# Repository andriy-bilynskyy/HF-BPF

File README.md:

# Short wave BPF

This is HW design of passive shortwave BPF 1.8MHz - 30MHz.

The schematic is based on 1.8MHz 7-th order elliptic HPF and 30MHz 7-th order elliptic LPF.

Input output filter resistance is 50 Ohms.

Loses in band-pass are less than -6.8dB. Loses at 60MHz and more are more than -80 dB. The same situation for frequencies lower than  1MHz - -80dB.

The design is created to use together with SDR receivers due to problematic reception of shot-wave bands in city conditions. This situation is mainly caused by huge noise from different switch power converters/inverters at low frequencies and FM radios at high frequencies.

## Folder structure

- **HF-BPF.asc** - LTspice simulation.  https://www.analog.com/en/design-center/design-tools-and-calculators/ltspice-simulator.html

- **HF-BPF.pro** - KiCad project. https://kicad.org/

- **HF-BPF.sch** - KiCad schematic.

- **HF-BPF.kicad_pcb** - KiCad PCB.

- **HF-BPF.net** - KiCad net-list file.

- **Manufacture** - Gerber files for PCB manufacturing. PCB manufacture https://www.elecrow.com/pcb-manufacturing.html

# Amplitude-frequency characteristic

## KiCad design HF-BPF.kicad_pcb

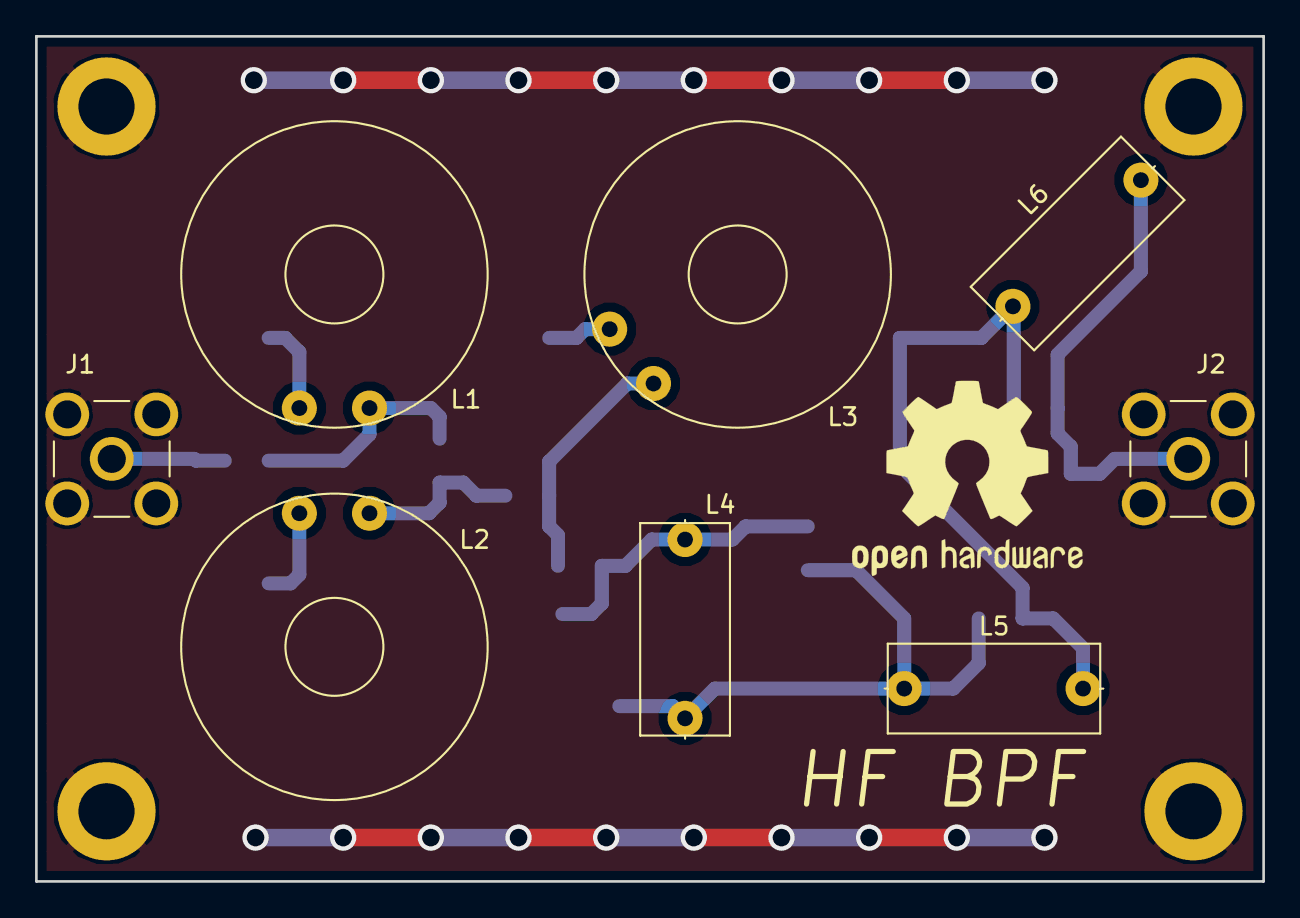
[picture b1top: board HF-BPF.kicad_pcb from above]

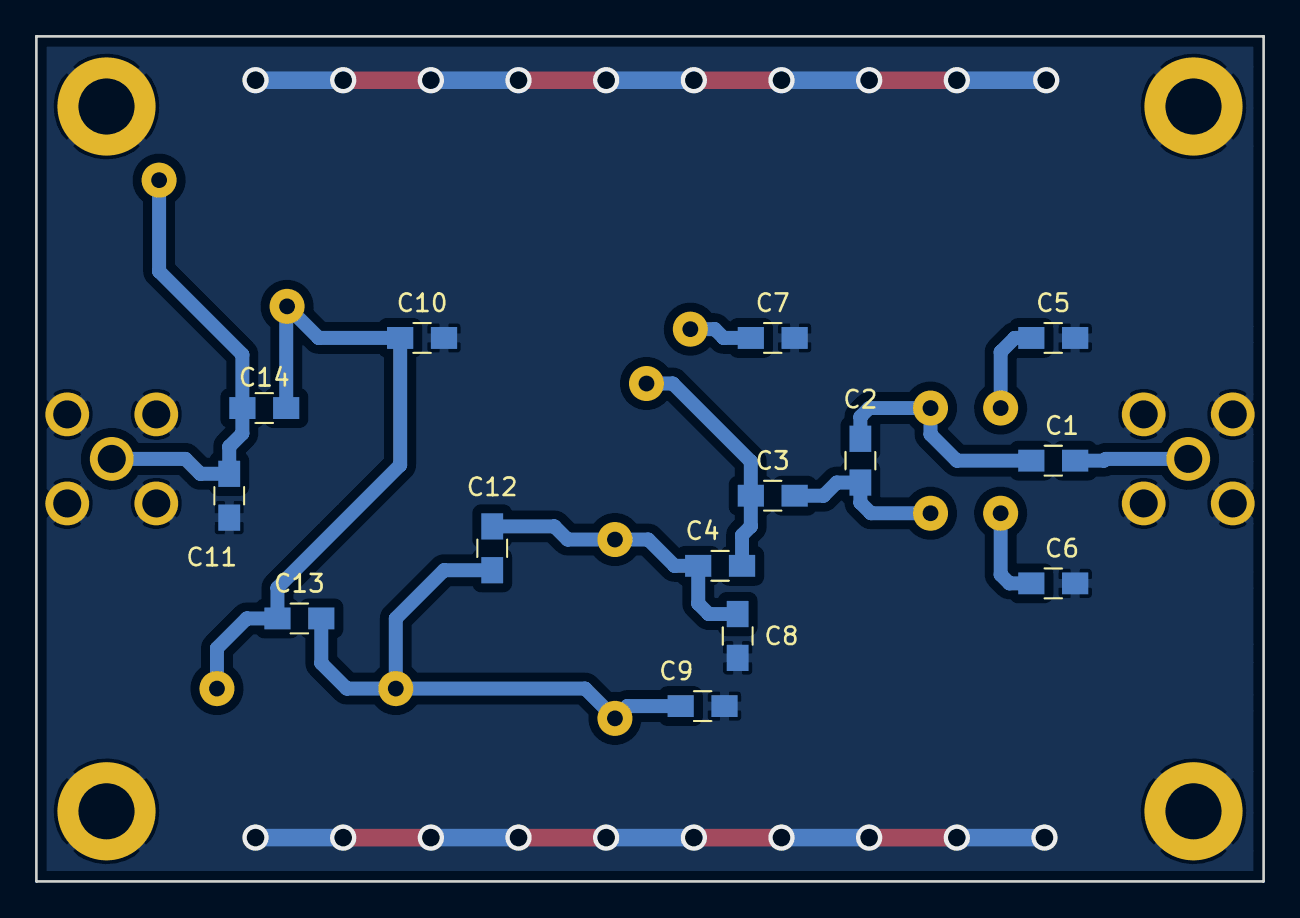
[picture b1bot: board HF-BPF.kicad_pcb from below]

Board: 2 copper layers, 70.0 x 48.2 mm, 22 parts (14 on the bottom side), 12 nets.

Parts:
C1, C4: 2.2nF; C_0805_HandSoldering
C2, C3: 1.5nF; C_0805_HandSoldering
C5: 33nF; C_0805_HandSoldering
C6, C7: 10nF; C_0805_HandSoldering
C8: 82pF; C_0805_HandSoldering
C9: 180pF; C_0805_HandSoldering
C10: 150pF; C_0805_HandSoldering
C11: 68pF; C_0805_HandSoldering
C12: 4.7pF; C_0805_HandSoldering
C13: 22pF; C_0805_HandSoldering
C14: 15pF; C_0805_HandSoldering
J1, J2: SMA-15; SMA_THT_Jack_Straight
L1: 3.2uH; L_Toroid_Horizontal_D17.3mm_P15.24mm_Bourns_2000
L2: 2.5uH; L_Toroid_Horizontal_D17.3mm_P15.24mm_Bourns_2000
L3: 3.6uH; L_Toroid_Horizontal_D17.3mm_P15.24mm_Bourns_2000
L4: 370nH; L_Axial_L12.0mm_D5.0mm_P15.24mm_Horizontal_Fastron_MISC
L5: 380nH; L_Axial_L12.0mm_D5.0mm_P15.24mm_Horizontal_Fastron_MISC
L6: 360nH; L_Axial_L12.0mm_D5.0mm_P15.24mm_Horizontal_Fastron_MISC

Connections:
GND: C5.1, C6.1, C7.1, C8.1, C9.1, C10.1, C11.1, J1.2, J2.2
unnamed: C1.1, C2.2, L1.1
unnamed: C1.2, J1.1
unnamed: C2.1, C3.2, L2.1
unnamed: C3.1, C4.2, L3.1
unnamed: C5.2, L1.2
unnamed: C6.2, L2.2
unnamed: C7.2, L3.2
unnamed: C10.2, C13.1, C14.2, L5.2, L6.1
unnamed: C11.2, C14.1, J2.1, L6.2
unnamed: C9.2, C12.1, C13.2, L4.2, L5.1
unnamed: C4.1, C8.2, C12.2, L4.1

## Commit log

2020-02-11 Initial commit.
    Calculations based on:
    https://vpayaem.ru/information6_2.html
2020-02-11 Add gitingore for generated files.
2020-02-12 Add inductors data.
    Calculations based on:
    https://coil32.net/
2020-02-12 Add PCB artwork.
2020-02-13 Add manufacture files.
2020-02-13 Add License and readme.
2020-02-13 Update readme.
2020-03-08 Update to kicad 5.
